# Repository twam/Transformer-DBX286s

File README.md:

DBX 286S Toroidal Transformer Retrofit
===

[![CC BY-SA 4.0][cc-by-sa-shield]][cc-by-sa]

This work is licensed under a [Creative Commons Attribution-NonCommercial-ShareAlike 4.0 International License][cc-by-sa].

[![CC BY-SA 4.0][cc-by-sa-image]][cc-by-sa]

[cc-by-sa]: http://creativecommons.org/licenses/by-nc-sa/4.0/
[cc-by-sa-image]: https://licensebuttons.net/l/by-nc-sa/4.0/88x31.png
[cc-by-sa-shield]: https://img.shields.io/badge/License-CC%20BY--NC--SA%204.0-lightgrey.svg

## Notes

Pictures show a 15 VA transformer from [talema](https://talema.com). This has more power than actually required. 10 VA and 7 VA versions should also fit on the PCB.

## Bill of materials

* Transformer, e.g. [70055K](https://talema.com/wp-content/uploads/datasheets/70000K-72400K.pdf). Smaller power (10 VA and 7 VA) and even smaller voltages (2x 18 V) might also work, but untested.
* 2 Faston Tabs from TE, 1217332-1, e.g. [571-1217332-1
 from Mouser](https://www.mouser.de/ProductDetail/571-1217332-1)
* Fuse Holder, e.g. [C58066 from LCSC](https://lcsc.com/product-detail/Fuse-Holders_Xucheng-Elec-C58066_C58066.html)
* Connector from MOLEX, 22272021, e.g. [C293316 from LCSC](https://lcsc.com/product-detail/Wire-To-Board-Wire-To-Wire-Connector_MOLEX-22272021_C293316.html)
* Glass fuse
* M4 Screws
* Cables

## Images

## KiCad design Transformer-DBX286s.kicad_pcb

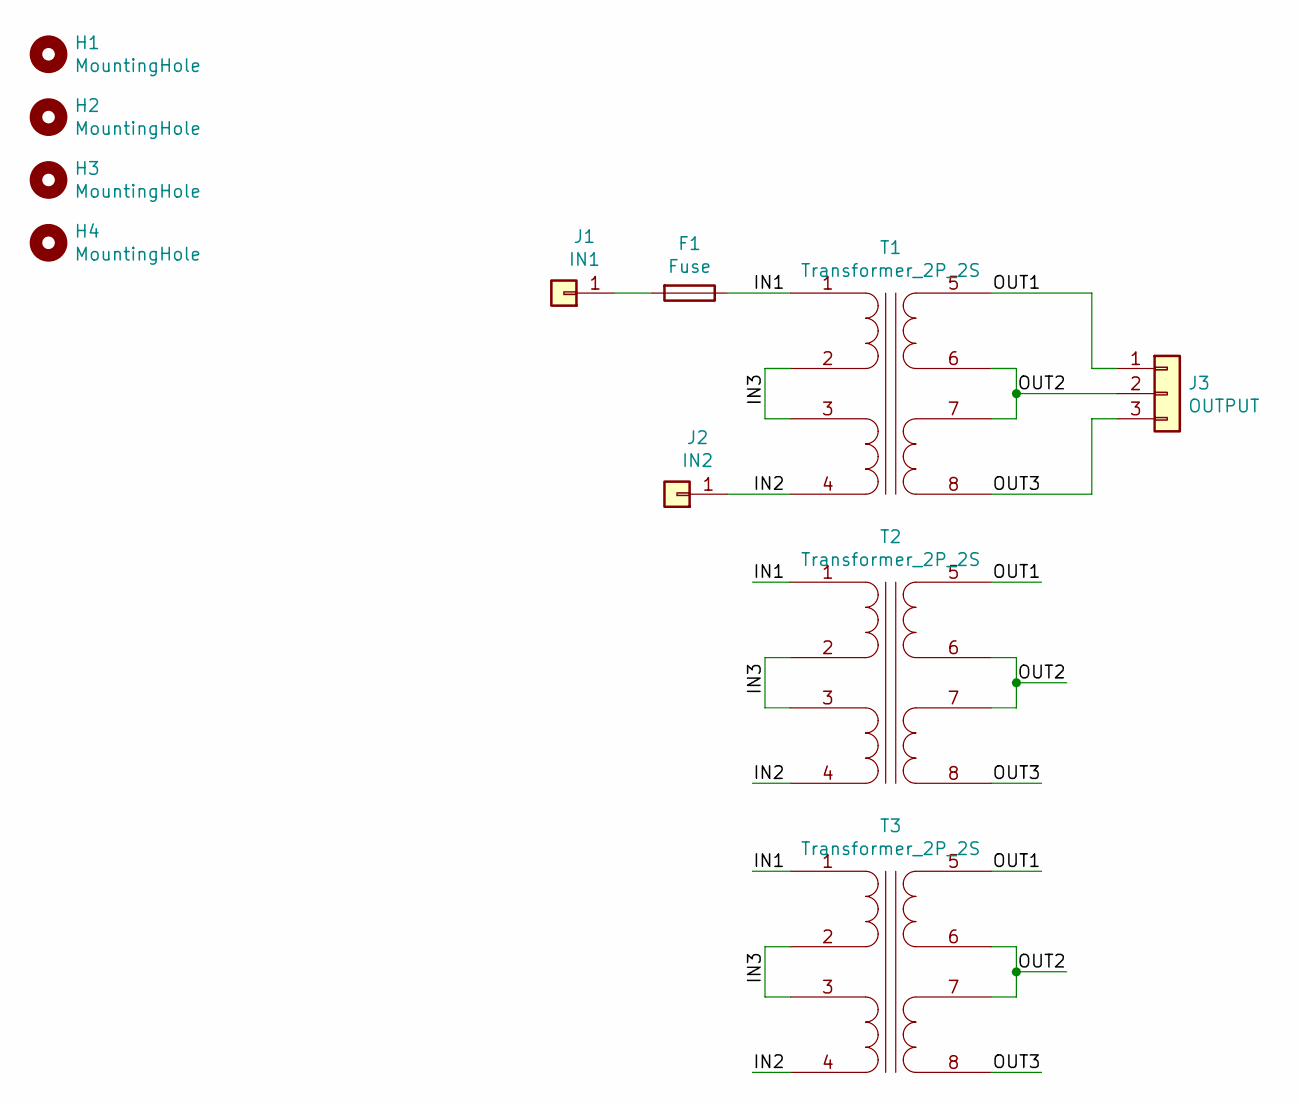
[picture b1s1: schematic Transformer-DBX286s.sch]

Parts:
F1: Fuse; Fuseholder_Cylinder-5x20mm_Schurter_0031_8201_Horizontal_Op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
H1, H2, H3, H4: MountingHole; MountingHole_4.3mm_M4
J1: IN1; TE_1217332-1
J2: IN2; TE_1217332-1
J3: OUTPUT; Molex_KK-254_AE-6410-03A_1x03_P2.54mm_Vertical
T1: Transformer_2P_2S; Talema_7xxxx_15VA
T2: Transformer_2P_2S; Talema_7xxxx_10VA
T3: Transformer_2P_2S; Talema_7xxxx_7VA

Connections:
/IN1: F1.1, T1.1 (IN1A), T2.1 (IN1A), T3.1 (IN1A)
/IN2: J2.1, T1.4 (OUT2B), T2.4 (OUT2B), T3.4 (OUT2B)
/IN3: T1.2 (IN1B), T1.3 (OUT2A), T2.2 (IN1B), T2.3 (OUT2A), T3.2 (IN1B), T3.3 (OUT2A)
/OUT1: J3.1, T1.5 (OUT1A), T2.5 (OUT1A), T3.5 (OUT1A)
/OUT2: J3.2, T1.6 (OUT1B), T1.7 (OUT2A), T2.6 (OUT1B), T2.7 (OUT2A), T3.6 (OUT1B), T3.7 (OUT2A)
/OUT3: J3.3, T1.8 (OUT2B), T2.8 (OUT2B), T3.8 (OUT2B)
unnamed: F1.2, J1.1

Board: 2 copper layers, 11 parts (0 on the bottom side), 7 nets, no tracks yet.

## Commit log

2021-05-15 Add README, Images & Mount
2021-05-15 Add BOM
